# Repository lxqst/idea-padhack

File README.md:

# idpad / hackpad

idpad is a hackpad with 5 keys , one rottary encorder and an 128x32 oled display

it serves as my first ever self made electronics projekt.

## FEATURES;

- 128x32 oled screen
- rotary encorder
- 5 keys

 ## CAD Models:
 
two pises one body where everything fits in and one top plate that closes it with 4 holes to screw it togheter.

Made in  FReeCAD

## PCB

Here is everything related to the pcb. Made in kicad

Schematic

PCB

   "
" />

## Firmware

The hackpad uses QMK Firmware

-The rotary encorder controlls the volumm and when pressed down it mutes everything
- the switches hafe following functions:
- skiping to the next song
- alt F4 shortcut
- snipping tool shortcut
- F13 button wich you can use for anything
- discord mute 

the oled display curently shows a pixel art picture
wich i may edit in the future

## BOM

- 5x Cherry MX Switches
- 5x Keycaps
- 4x heatset inserts
- 4x bolts
- 6x 1N4148 DO-35 Diodes
- 1x 0.91" 128x32 OLED Display
- 1x EC11 Rotary Encoder
- 1x XIAO RP2040
-  1x Case
- PCB

## Extra stuff

  idk guid says not sure what to put here

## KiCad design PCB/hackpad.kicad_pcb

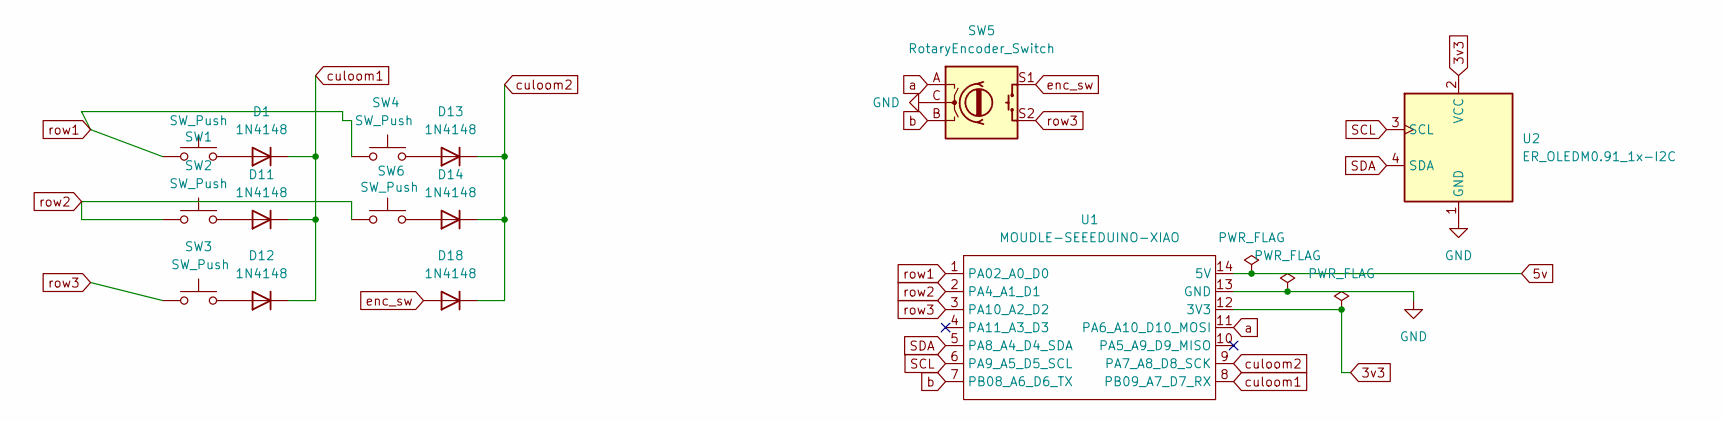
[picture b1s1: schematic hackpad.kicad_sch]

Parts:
D1, D11, D12, D13, D14, D18: 1N4148; D_DO-35_SOD27_P7.62mm_Horizontal
SW1, SW2, SW3, SW4, SW6: SW_Push; SW_Cherry_MX_1.00u_PCB
SW5: RotaryEncoder_Switch; RotaryEncoder_Alps_EC11E-Switch_Vertical_H20mm
U1: MOUDLE-SEEEDUINO-XIAO; XIAO-Generic-Hybrid-14P-2.54-21X17.8MM
U2: ER_OLEDM0.91_1x-I2C

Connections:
3v3: U1.12 (3V3), U2.2 (VCC)
5v: U1.14 (5V)
GND: SW5.C, U1.13 (GND), U2.1 (GND)
unnamed: D1.2 (A), SW1.2
unnamed: D11.2 (A), SW2.2
unnamed: D12.2 (A), SW3.2
unnamed: D13.2 (A), SW4.2
unnamed: D14.2 (A), SW6.2
SCL: U1.6 (PA9_A5_D5_SCL), U2.3 (SCL)
SDA: U1.5 (PA8_A4_D4_SDA), U2.4 (SDA)
a: SW5.A, U1.11 (PA6_A10_D10_MOSI)
b: SW5.B, U1.7 (PB08_A6_D6_TX)
culoom1: D1.1 (K), D11.1 (K), D12.1 (K), U1.8 (PB09_A7_D7_RX)
culoom2: D13.1 (K), D14.1 (K), D18.1 (K), U1.9 (PA7_A8_D8_SCK)
enc_sw: D18.2 (A), SW5.S1
row1: SW1.1, SW4.1, U1.1 (PA02_A0_D0)
row2: SW2.1, SW6.1, U1.2 (PA4_A1_D1)
row3: SW3.1, SW5.S2, U1.3 (PA10_A2_D2)

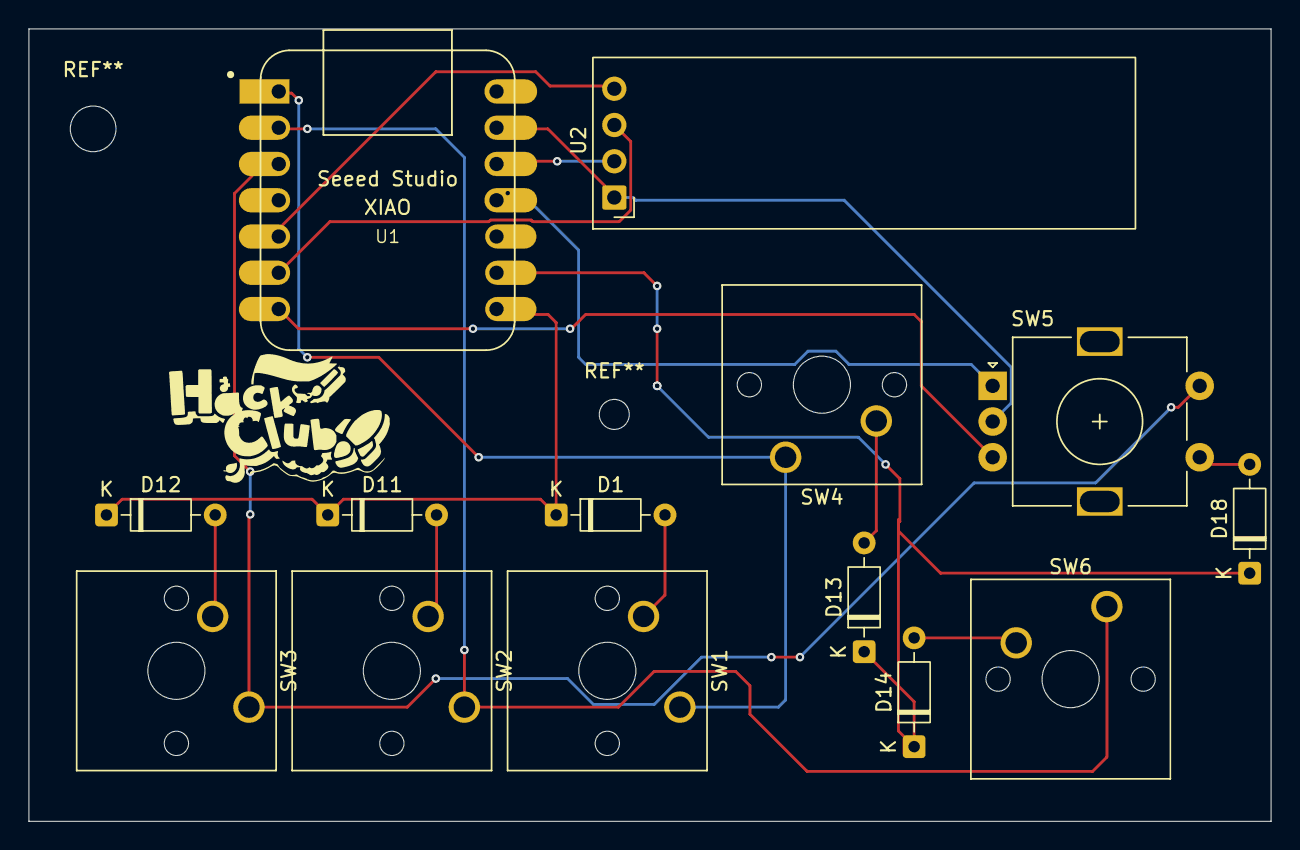
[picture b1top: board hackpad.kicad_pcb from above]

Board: 2 copper layers, 87.0 x 55.5 mm, 14 parts (0 on the bottom side), 17 nets.
